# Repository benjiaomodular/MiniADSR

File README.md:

# MiniADSR

A four-parameter envelope generator based on Rene Schmitz' [The Fastest Envelope in the West](https://www.schmitzbits.de/adsr.html).

# Versions

## 1.0.1
Quick fixes for v1.0
- Fixed connection of R7 to Q2 pin 1
- Updated C2 value to 10uF
- Change sustain pot from 1M to 10k
- C3 from 100uF to 1uF
- Added version numbers
- Flipped power connectors 180deg to accomodate larger IDC connectors.

## 1.0
Initial design.

### Issues
- Wrong connection from R7
- Wrong value for C3 and Sustain pot

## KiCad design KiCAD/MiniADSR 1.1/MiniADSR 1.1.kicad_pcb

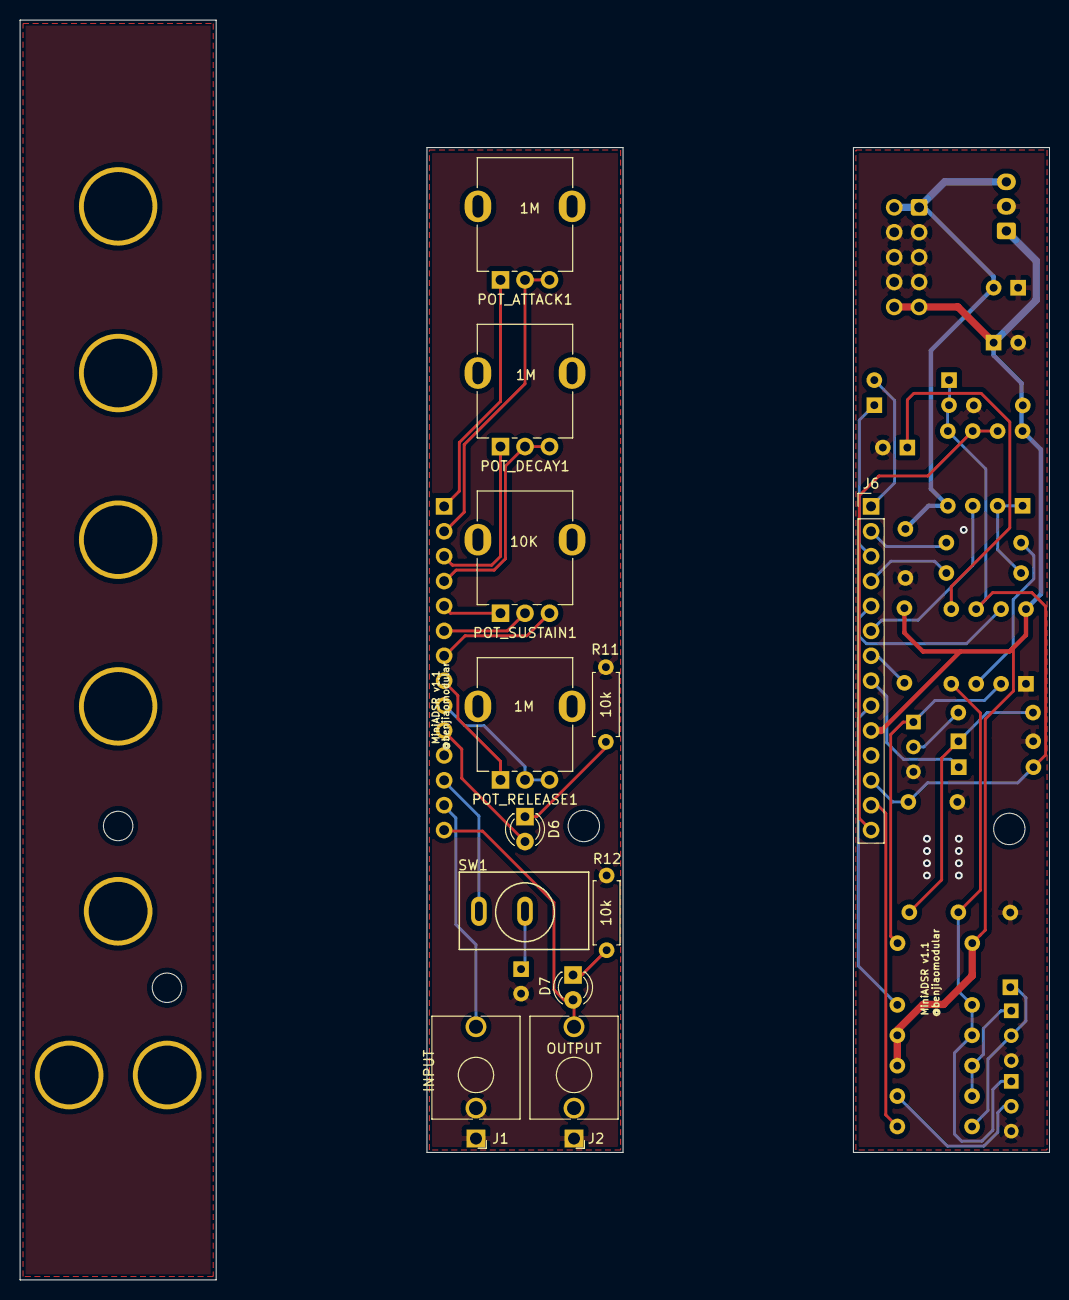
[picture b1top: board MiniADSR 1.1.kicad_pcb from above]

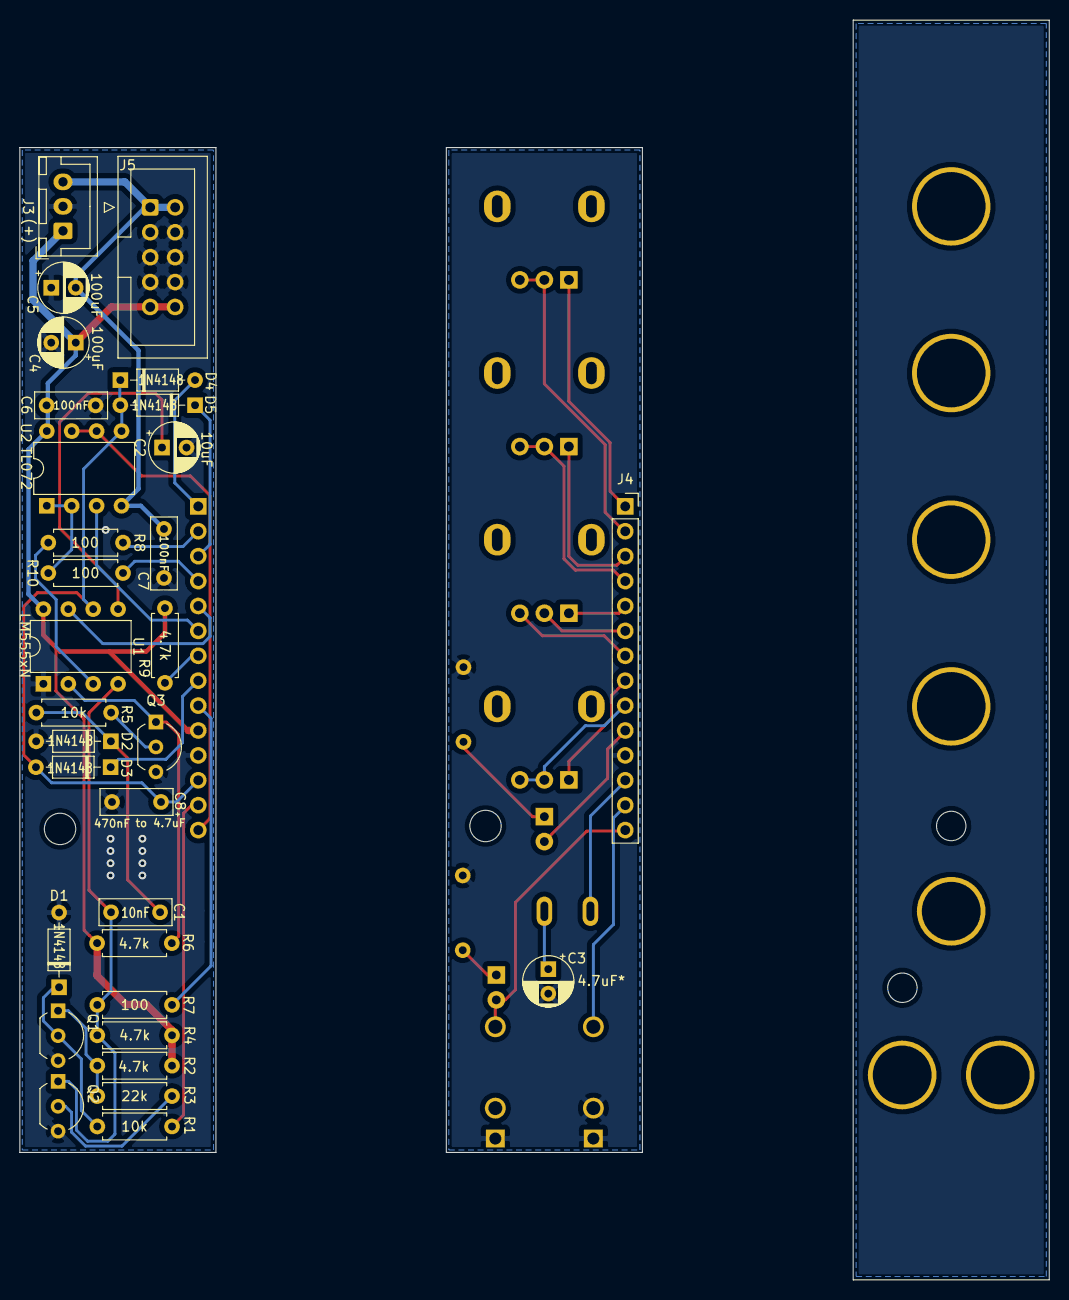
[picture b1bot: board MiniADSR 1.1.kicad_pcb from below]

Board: 2 copper layers, 105.0 x 128.5 mm, 43 parts (31 on the bottom side), 42 nets.

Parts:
C1: 10nF; C_Rect_L7.2mm_W2.5mm_P5.00mm_FKS2_FKP2_MKS2_MKP2
C2: 10uF; CP_Radial_D5.0mm_P2.50mm
C3: 4.7uF*; CP_Radial_D5.0mm_P2.50mm
C4, C5: 100uF; CP_Radial_D5.0mm_P2.50mm
C6, C7: 100nF; C_Rect_L7.2mm_W2.5mm_P5.00mm_FKS2_FKP2_MKS2_MKP2
C8: 470nF; Capacitor_Rect_L7.2mm_W2.5mm_P5.00mm
D1, D2, D3, D4, D5: 1N4148; D_DO-35_SOD27_P7.62mm_Horizontal
D6: PWR_LED; LED_D3.0mm
D7: OUTPUT_LED; LED_D3.0mm
J1: INPUT; AudioJack_3.5mm
J2: OUTPUT; AudioJack_3.5mm
J3: JST_BUS; JST_XH_B3B-XH-A_1x03_P2.50mm_Vertical
J4: ControlBoard_Pins; PinSocket_1x14_P2.54mm_Vertical
J5: IDC_BUS; IDC-Header_2x05_P2.54mm_Vertical
J6: MainBoard_Pins; PinHeader_1x14_P2.54mm_Vertical
POT_ATTACK1: 1M; Potentiometer_RV09
POT_DECAY1: 1M; Potentiometer_RV09
POT_RELEASE1: 1M; Potentiometer_RV09
POT_SUSTAIN1: 10k; Potentiometer_RV09
Q1, Q2, Q3: BC547; TO-92_Inline_Wide
R1, R5, R11, R12: 10k; R_Axial_DIN0207_L6.3mm_D2.5mm_P7.62mm_Horizontal
R2, R4, R6, R9: 4.7k; R_Axial_DIN0207_L6.3mm_D2.5mm_P7.62mm_Horizontal
R3: 22k; R_Axial_DIN0207_L6.3mm_D2.5mm_P7.62mm_Horizontal
R7, R8, R10: 100; R_Axial_DIN0207_L6.3mm_D2.5mm_P7.62mm_Horizontal
SW1: SW_DIP_x01; ToggleSwitch_MTS-101_SPST
U1: LM555xN; DIP-8_W7.62mm
U2: TL072; DIP-8_W7.62mm

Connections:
+12V: C4.1, C6.1, J3.1, J5.9, J5.10, J6.10, R2.2, R4.2, R6.2, R9.2, U1.8, U2.8
-12V: C5.2, C7.2, J3.3, J5.1, J5.2, U2.4
A1: J1.T, J4.13
A2: D7.2, J2.T, J4.14
A3: J4.1, POT_ATTACK1.1
A4: J4.2, POT_ATTACK1.2, POT_ATTACK1.3
A5: J4.3, POT_DECAY1.1
A6: J4.4, POT_DECAY1.2, POT_DECAY1.3
A7: J4.5, POT_SUSTAIN1.1
A8: J4.6, POT_SUSTAIN1.2
A9: J4.7, POT_SUSTAIN1.3
A10: J4.8, POT_RELEASE1.1
A11: J4.9, POT_RELEASE1.2, POT_RELEASE1.3
A12: J4.12, SW1.1
A_VCC: D6.2, J4.10
B1: J6.13, R1.2
B2: J6.14, U2.6, U2.7
B3: D4.2, J6.1
B4: J6.2, R8.2
B5: D5.1, J6.3
B6: J6.4, R10.2
B7: J6.5, U1.7
B8: J6.6, U2.3
B9: J6.7, R9.1
B10: D3.1, J6.8
B11: J6.9, R7.2
B12: C8.2, D3.2, D4.1, D5.2, J6.12, U1.6, U2.5
GND1: C3.2, J1.S, J1.TN, J2.S, J4.11, R11.1, R12.1
GND2: C2.2, C4.2, C5.1, C6.2, C7.1, C8.1, D1.2, D2.2, J3.2, J5.3, J5.4, J5.5, J5.6, J5.7, J5.8, J6.11, Q1.3, Q2.3, Q3.3, U1.1
unnamed: C1.1, D2.1, R5.1
unnamed: C1.2, Q2.1, R4.1, R7.1, U1.4
unnamed: C2.1, U1.5
unnamed: C3.1, SW1.2
unnamed: D1.1, Q1.2, R1.1
unnamed: D6.1, R11.2
unnamed: D7.1, R12.2
unnamed: Q1.1, R2.1, R3.1
unnamed: Q2.2, R3.2
unnamed: Q3.1, R6.1, U1.2
unnamed: Q3.2, R5.2
unnamed: R8.1, U1.3
unnamed: R10.1, U2.1, U2.2

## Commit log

2022-01-07 Updated front panel labels
2022-01-09 Added fabrication files
2022-01-17 Started 1.1, refined labels
2022-01-17 Adjusted graphic line thickness
2022-01-17 Tweaked front panel print
2022-01-19 Added labels to pot footprints
2022-01-19 nudged IC labels
2022-01-19 Added fixes after fist build
2022-01-19 Added disclaimer for not validated builds
2022-01-19 Added version number
2022-01-20 increased c3 as recommended by in original design
2022-01-20 Redesigned PCB layout, added cap for longer decay
2022-02-01 Added v1.0.1 for minor corrections on first version
2022-02-01 Updated docs on versions
2022-02-01 typo
2022-02-01 Formatting update to readme
2022-02-01 Added svg of 1.0.1
2022-02-04 Flipped power connectors for v1.0.1
2022-02-04 Updated readme notes
2022-02-04 added license file
2022-02-07 Updated license date
2022-02-19 Updated readme for 1.0.1
